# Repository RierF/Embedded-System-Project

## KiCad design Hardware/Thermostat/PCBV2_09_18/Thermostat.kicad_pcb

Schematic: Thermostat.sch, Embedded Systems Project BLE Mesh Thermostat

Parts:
AE1: Antenna_Loop; NFC_Antenna
BT1, BT2: Battery_Cell; Pin_Header_Straight_1x02_Pitch2.54mm
C1, C3, C15, C19, C22, C23, C24: 4,7µ; C_0603
C2, C5: 4.7µ; C_0603
C4: 0,1µ; C_0603
C6: 0,01µ; C_0603
C7, C8, C9, C10, C11, C12: 100n; C_0603
C13, C14: 300p; C_0603
C16, C17, C18, C20, C21: 4,7µ; C_1206
D1, D2: LED; LED_0603
J1: Conn_02x05_Odd_Even; Pin_Header_Straight_2x05_Pitch2.54mm
J2: USB_OTG; USB_Micro-B_Molex-105017-0001
J3: Conn_02x03_Odd_Even; Pin_Header_Straight_2x03_Pitch2.54mm
L1: 22µ; L_0603
L2: L_Small; L_0603
R1, R2: 75k; R_0603
R3: 2k; R_0603
R4, R5: 50k; R_0603
R6, R12, R15: 4,42M; R_0603
R7: 470R; R_0603
R8: 15M; R_0603
R9, R11: 5,6M; R_0603
R10: 4.02M; R_0603
R13: 1,43M; R_0603
R14: 4,22M; R_0603
R16: 180r; R_0603
R17, R18: 10k; R_0603
R19: 604k; R_0603
R20: 300k; R_0603
SW1: Rotary_Encoder; RotaryEncoder_Alps_EC11E-Switch_Vertical_H20mm
SW2, SW3, SW4: SW_Push; SW_SPST_B3SL-1022P
U1: MCP73831-2-OT; SOT-23-5
U2: BQ25504; QFN-16-1EP_3x3mm_P0.5mm_EP1.8x1.8mm
U3: BME280; Bosch_LGA-8_2.5x2.5mm_P0.65mm_ClockwisePinNumbering
U4: ACN52832

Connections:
BATT: BT1.1, BT2.1, C5.1, U1.3 (VBAT), U2.14
CLK: J3.1, R17.1, U3.4, U4.27
GND: BT1.2, BT2.2, C1.1, C2.1, C3.2, C4.2, C5.2, C6.2, C7.1, C8.1, C9.2, C10.2, C11.2, C12.2, C13.2, C14.2, C15.2, C16.2, C17.2, C18.2, C19.1, C20.1, C21.1, C22.1, C23.1, C24.1, D2.1, J1.3, J1.5, J1.9, J2.5, J3.5, R4.2, R5.2, R11.1, R15.2, R19.1, R20.2, SW1.C, SW2.1, SW3.1, SW4.1, U2.1, U2.5, U2.13, U3.1, U3.5, U3.7, U4.1, U4.13, U4.35
LED: R16.2, U4.26
unnamed: AE1.1, C14.1, U4.19
unnamed: AE1.2, C13.1, U4.18
unnamed: C6.1, U2.4
unnamed: C8.2, L2.2, U3.8
unnamed: D1.1, R7.1
unnamed: D2.2, R16.1
unnamed: J2.2, R2.2, R5.1
unnamed: J2.3, R1.2, R4.1
unnamed: L1.2, U2.16
unnamed: R3.1, U1.5 (PROG)
unnamed: R3.2, U1.2 (VSS)
unnamed: R6.2, R8.2, U2.3
unnamed: R7.2, U1.1 (STAT)
unnamed: R9.2, R10.1, U2.6
unnamed: R10.2, R12.2, R13.1, U2.7
unnamed: R11.2, R12.1, U2.8
unnamed: R13.2, R14.1, U2.9
unnamed: R14.2, R15.1, U2.10
unnamed: R8.1, R19.2
unnamed: R9.1, R20.1
PUSH_BTN: SW2.2, SW3.2, SW4.2, U4.30
RESET: J1.10, U4.31
ROT_A: SW1.A, U4.10
ROT_B: SW1.B, U4.11
SDA: J3.3, R18.2, U3.3, U4.29
STOR: C3.1, C4.1, C7.2, C9.1, C10.1, C11.1, C12.1, C15.1, C16.1, C17.1, C18.1, C19.2, C20.2, C21.2, C22.2, C23.2, C24.2, J1.1, J3.6, L2.1, R1.1, R2.1, R17.2, R18.1, U2.15, U3.2, U3.6, U4.12, U4.23, U4.24, U4.32
SWDCLK: J1.4, U4.34
SWDIO: J1.2, U4.33
SWO: J1.6, U4.28
Solar_GND: J3.4
Solar_VCC: C1.2, J3.2, L1.1, R6.1, U2.2
VUSB: C2.2, D1.2, J2.1, U1.4 (VDD)

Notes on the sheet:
Energy Harvesting
To Solar
Buttons and Rotary Encoder
USB Battery
Combi Sensor
ACONNO nRF52 Chip
JTAG
Conn_peripherie Display and Solar

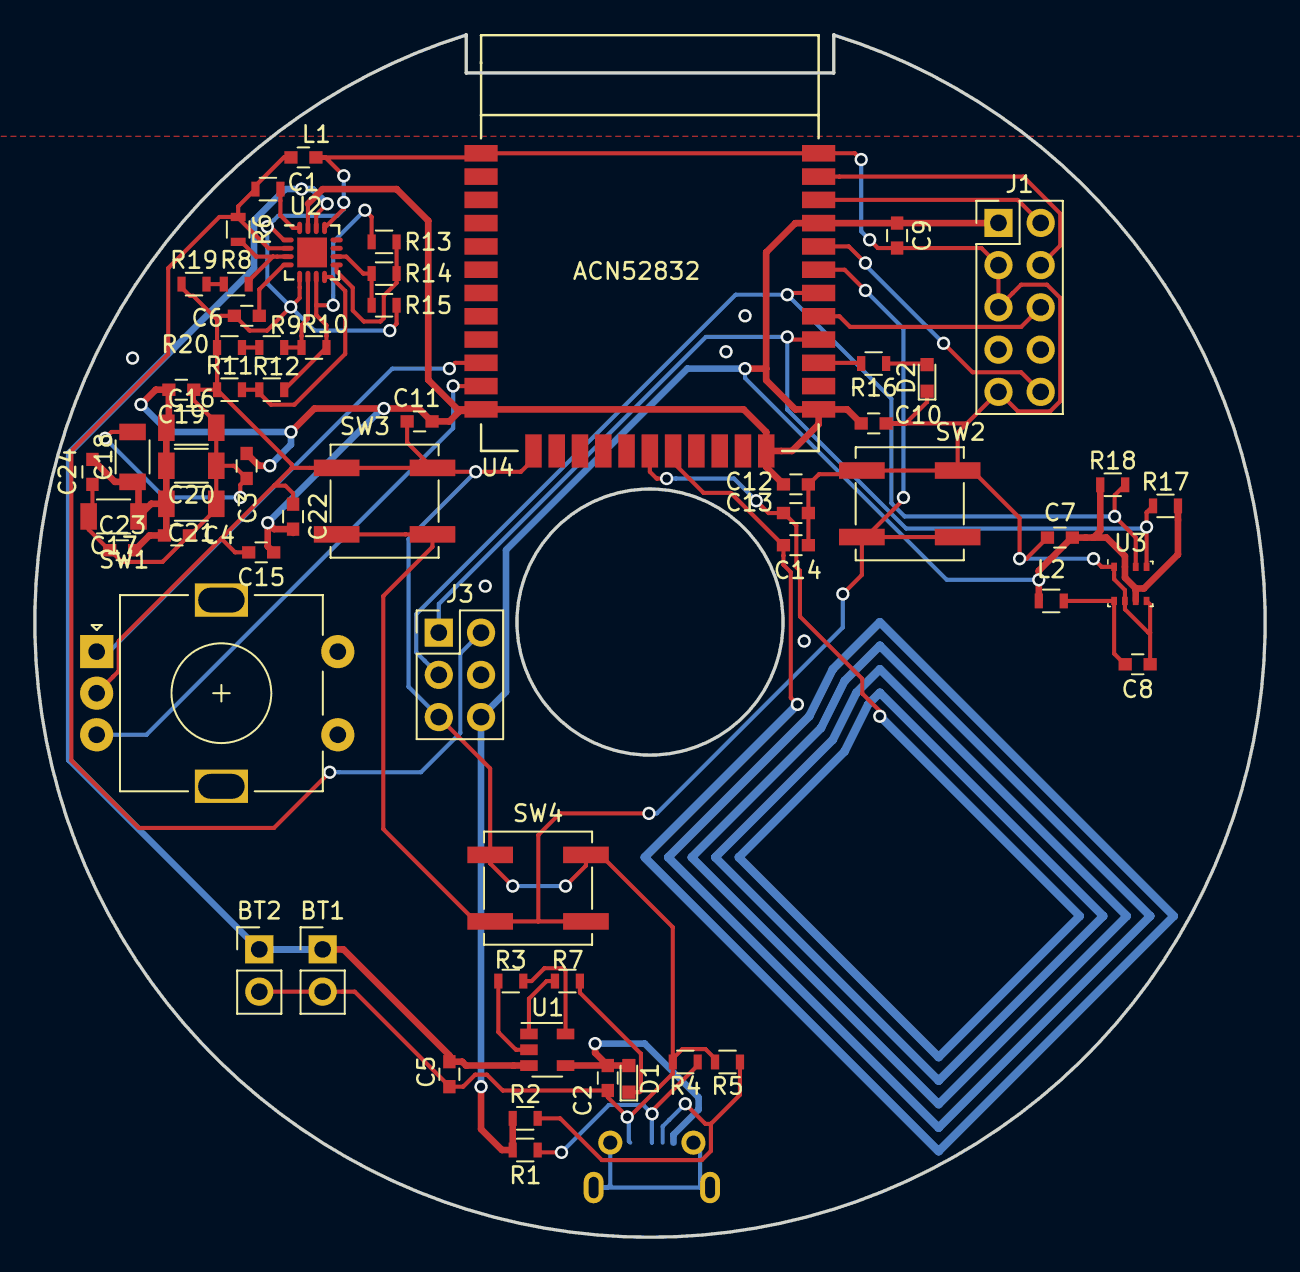
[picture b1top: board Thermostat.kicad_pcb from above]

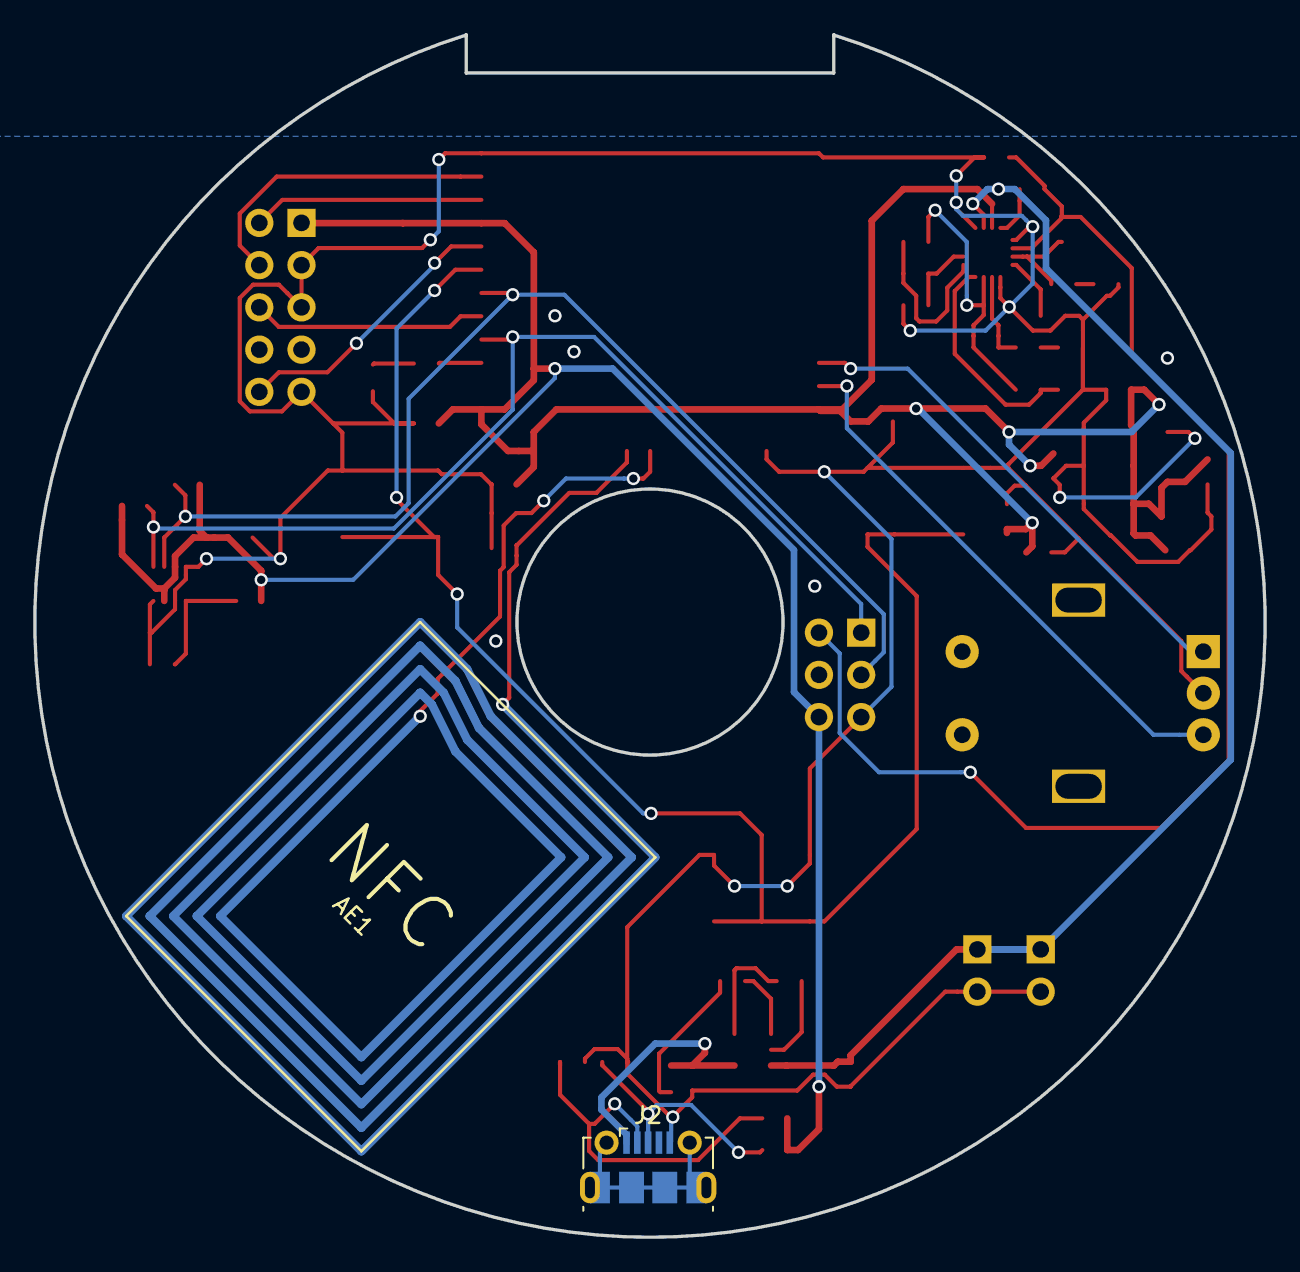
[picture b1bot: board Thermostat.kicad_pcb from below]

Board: 2 copper layers, 74.0 x 72.3 mm, 62 parts (2 on the bottom side), 35 nets.

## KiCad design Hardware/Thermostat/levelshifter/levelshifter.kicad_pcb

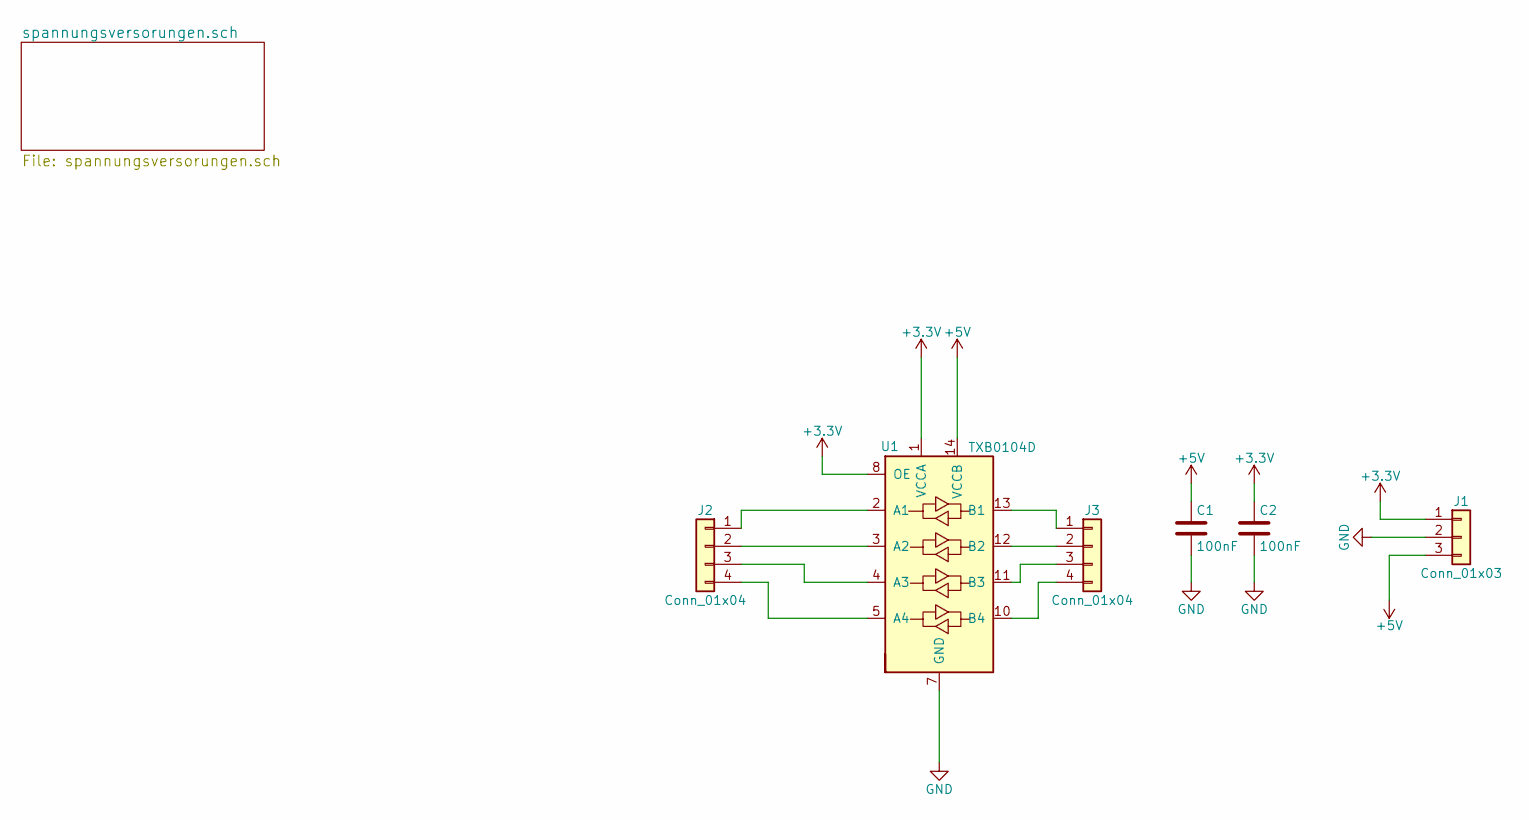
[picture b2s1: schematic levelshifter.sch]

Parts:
C1, C2: 100nF; C_0805_HandSoldering
J1: Conn_01x03; Pin_Header_Straight_1x03_Pitch2.54mm
J2, J3: Conn_01x04; Pin_Header_Straight_1x04_Pitch2.54mm
U1: TXB0104D; SOIC-14_3.9x8.7mm_Pitch1.27mm

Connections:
+3V3: C2.1, J1.1, U1.1 (VCCA), U1.8 (OE)
+5V: C1.1, J1.3, U1.14 (VCCB)
GND: C1.2, C2.2, J1.2, U1.7 (GND)
unnamed: J2.1, U1.2 (A1)
unnamed: J2.2, U1.3 (A2)
unnamed: J2.3, U1.4 (A3)
unnamed: J2.4, U1.5 (A4)
unnamed: J3.1, U1.13 (B1)
unnamed: J3.2, U1.12 (B2)
unnamed: J3.3, U1.11 (B3)
unnamed: J3.4, U1.10 (B4)

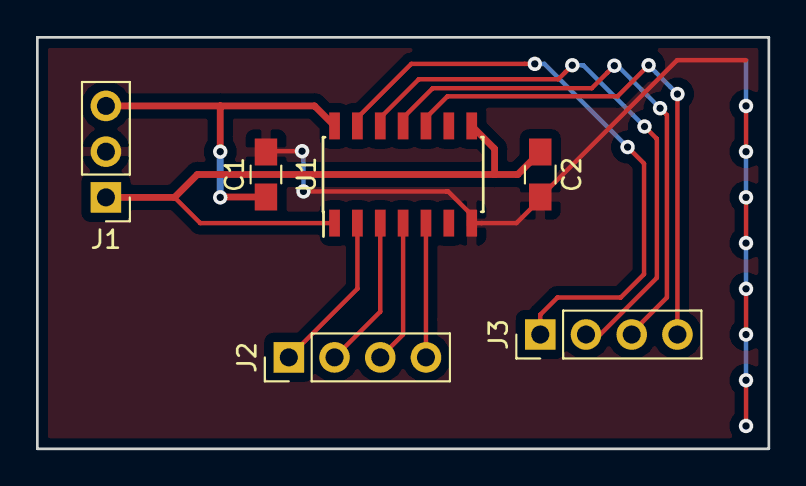
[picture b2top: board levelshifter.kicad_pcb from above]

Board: 2 copper layers, 40.6 x 22.9 mm, 6 parts (0 on the bottom side), 11 nets.

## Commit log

2019-06-08 Software and Hardware Files
